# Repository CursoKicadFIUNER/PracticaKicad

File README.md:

# PracticaKicad
Repositorio de curso Kicad en la FIUNER 2016
Nueva línea. JAB

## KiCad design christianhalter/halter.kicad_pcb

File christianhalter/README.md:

# PracticaKicad
Carpeta creada por Christian Halter

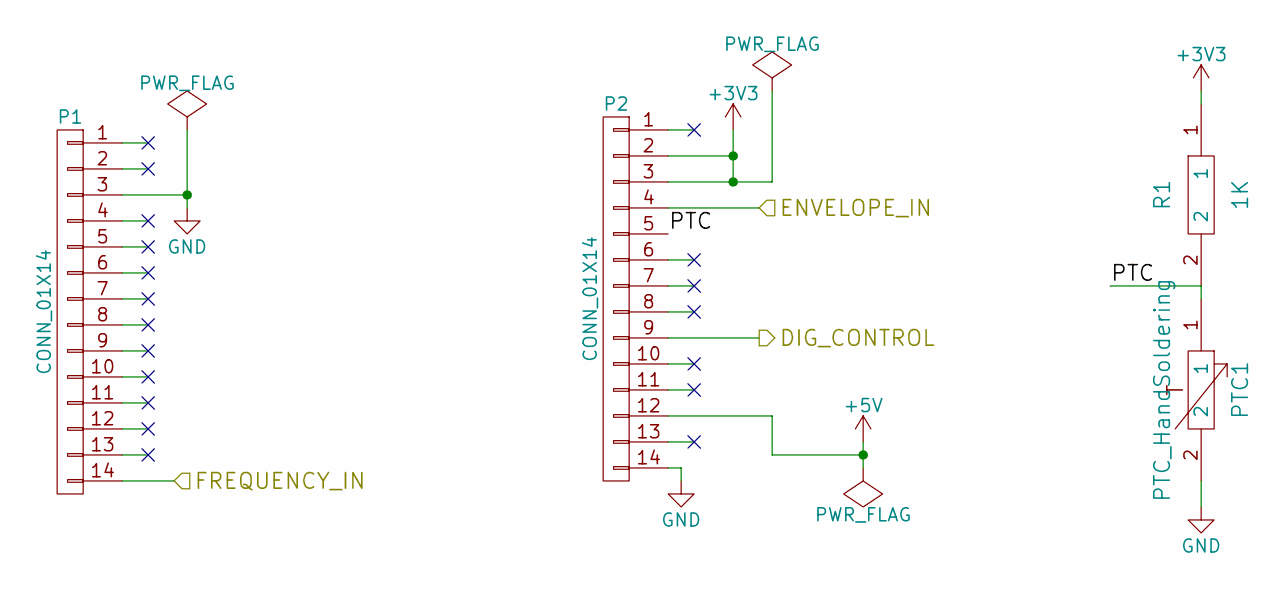
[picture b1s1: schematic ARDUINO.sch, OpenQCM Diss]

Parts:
P1, P2: CONN_01X14; PINHEAD1-14; Digikey/Mouser Value
PTC1: PTC_HandSoldering; R_0805_HandSoldering
R1: 1K; R_0805_HandSoldering; Digikey/Mouser Value

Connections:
+3V3: P2.2, P2.3, R1.1; also elsewhere on the board
+5V: P2.12; also elsewhere on the board
/ARDUINO/DIG_CONTROL: P2.9; also elsewhere on the board
/ARDUINO/ENVELOPE_IN: P2.4; also elsewhere on the board
/ARDUINO/FREQUENCY_IN: P1.14; also elsewhere on the board
/ARDUINO/PTC: P2.5, PTC1.1, R1.2
GND: P1.3, P2.14, PTC1.2; also elsewhere on the board

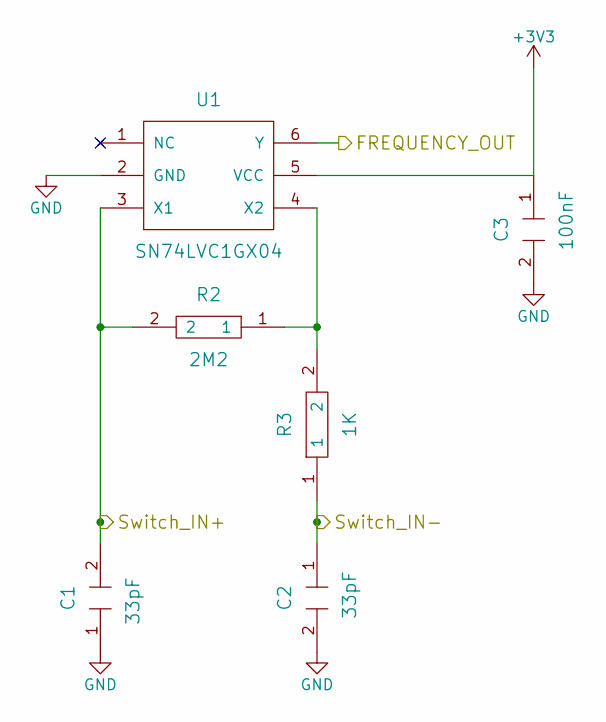
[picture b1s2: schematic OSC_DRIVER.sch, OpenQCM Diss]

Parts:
C1, C2: 33pF; C_0603_HandSoldering; Digikey/Mouser Value
C3: 100nF; C_0603_HandSoldering; Digikey/Mouser Value
R2: 2M2; R_0805_HandSoldering; Digikey/Mouser Value
R3: 1K; R_0805_HandSoldering; Digikey/Mouser Value
U1: SN74LVC1GX04; SOT-23-6; Digikey/Mouser Value

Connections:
+3V3: C3.1, U1.5 (VCC); also elsewhere on the board
/ARDUINO/FREQUENCY_IN: U1.6 (Y); also elsewhere on the board
/OSC_DRIVER/Switch_IN+: C1.2, R2.2, U1.3 (X1); also elsewhere on the board
/OSC_DRIVER/Switch_IN-: C2.1, R3.1; also elsewhere on the board
GND: C1.1, C2.2, C3.2, U1.2 (GND); also elsewhere on the board
unnamed: R2.1, R3.2, U1.4 (X2)

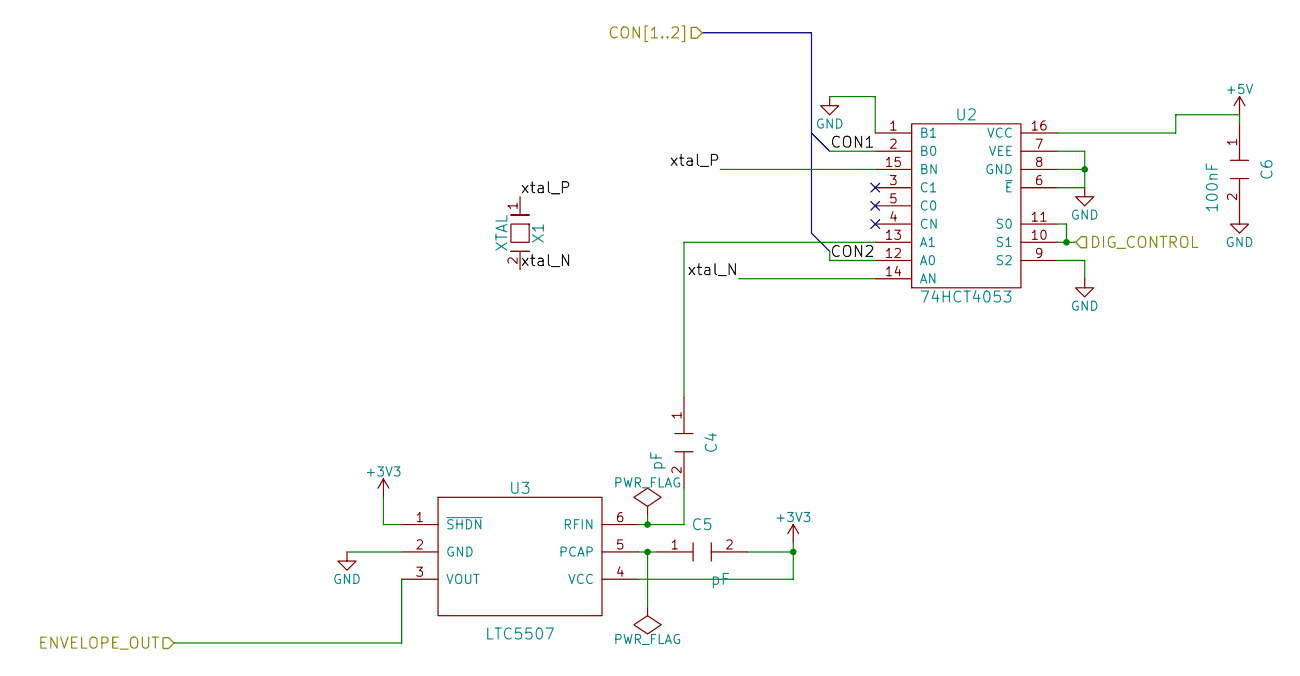
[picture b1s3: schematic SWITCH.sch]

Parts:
C4, C5: pF; C_0603_HandSoldering
C6: 100nF; C_0603_HandSoldering
U2: 74HCT4053; TSSOP16
U3: LTC5507; SOT-23-6
X1: XTAL; XTAL_con

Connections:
+3V3: C5.2, U3.1 (~SHDN), U3.4 (VCC); also elsewhere on the board
+5V: C6.1, U2.16 (VCC); also elsewhere on the board
/ARDUINO/DIG_CONTROL: U2.10 (S1), U2.11 (S0); also elsewhere on the board
/ARDUINO/ENVELOPE_IN: U3.3 (VOUT); also elsewhere on the board
/OSC_DRIVER/Switch_IN+: U2.12 (A0); also elsewhere on the board
/OSC_DRIVER/Switch_IN-: U2.2 (B0); also elsewhere on the board
/SWITCH/xtal_N: U2.14 (AN), X1.2
/SWITCH/xtal_P: U2.15 (BN), X1.1
GND: C6.2, U2.1 (B1), U2.6 (~E), U2.7 (VEE), U2.8 (GND), U2.9 (S2), U3.2 (GND); also elsewhere on the board
unnamed: C4.1, U2.13 (A1)
unnamed: C4.2, U3.6 (RFIN)
unnamed: C5.1, U3.5 (PCAP)

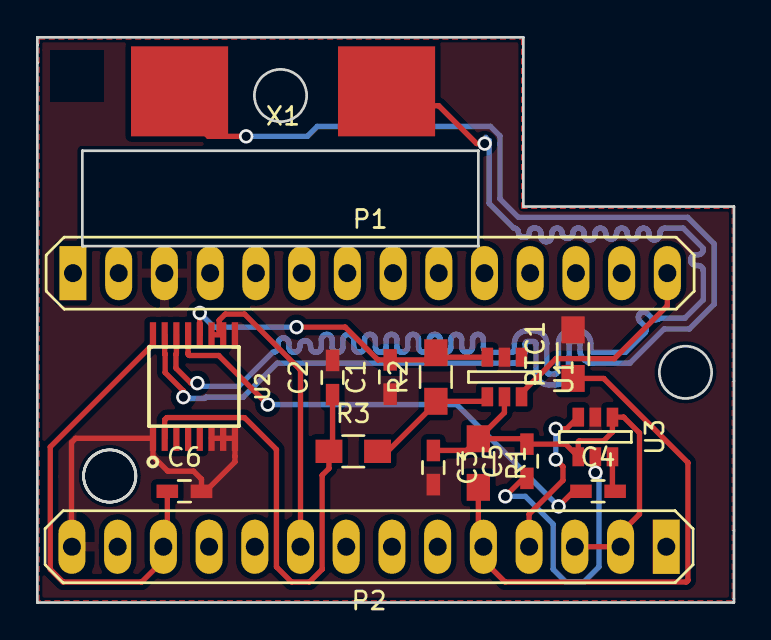
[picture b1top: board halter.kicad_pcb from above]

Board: 2 copper layers, 38.7 x 31.4 mm, 16 parts (0 on the bottom side), 15 nets.

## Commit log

2016-03-23 Archivos segunda practica OpenQCM
2016-03-23 Punto de partida de PCB OpenQCM
2016-03-27 Footprint capacitor 0603
2016-03-28 hola mundo
2016-03-28 Acá va lo mio. Cesario_Bruno
2016-03-28 archivo personal
2016-03-28 Carpeta personal christianhalter
2016-03-28 Va mi carpeta!
2016-03-28 carpeta prueba
2016-03-28 CariSosa
2016-03-28 Hola. Juani.
2016-03-28 Soy Jona
2016-03-28 Hola
2016-03-28 Realicé cambios en el archivo TestFile
2016-03-28 no message
2016-03-28 Hola2.0
2016-03-28 Juanito
2016-03-28 Gracias Ludio...!
2016-03-28 Ya tengo una.
2016-03-28 some changes
2016-03-28 Ej.2
2016-03-28 Craci
2016-03-28 Creación directorio proyecto de Cesario Bruno
2016-03-28 Jerarquia de Hojas Creacion de Libreria LTC5507
2016-03-28 Creacion proyecto
2016-03-28 Creacion Esquematico Switch_Envelope
2016-03-28 subhojas del projecto
2016-03-28 esquema
2016-03-28 Actualizacion
2016-03-28 va la tarea...
2016-03-28 cari sosa
2016-03-28 Actualizacion Final
2016-03-28 Cari
2016-03-28 componente nuevo
2016-03-28 Fin clase 2. Cración del footprint faltante y asociación del mismo
2016-03-28 Fin clase 2 faltante
2016-03-29 Comienzo PCB. Emplazamiento de componentes Error footprint PTC y crearlo
2016-03-29 Prueba de Ruteo PCB ambas capas. Finalizado.
2016-03-31 Archivos Kicad de la clase 2
2016-04-04 Miniactualización. No importa.
2016-04-04 Modificacion para inclusion de plantilla.
2016-04-04 Gerber
2016-04-04 Fin Clase 3. Generacion Nuevo PCB y Ruteo. Capa de Cobre. Archivos Gerber y Visualización.
2016-04-07 Carpeta de trabajo Juan Cruz GL.
    Raiz: Lo hecho en clase 4/4/16
    Re_intento: Repaso desde cero de lo realizado en la clase
2016-04-07 Ejercicio 3 JCGL
2016-04-09 modelos 3D ejercicio OpenQCM
2016-04-11 Libreria nueva
2016-04-11 Cambio de componente. Componente Multiparte. OK
2016-04-11 Diseño 3D y Visualizacion del modelo final. Generacion de archivo exportable VRML.
